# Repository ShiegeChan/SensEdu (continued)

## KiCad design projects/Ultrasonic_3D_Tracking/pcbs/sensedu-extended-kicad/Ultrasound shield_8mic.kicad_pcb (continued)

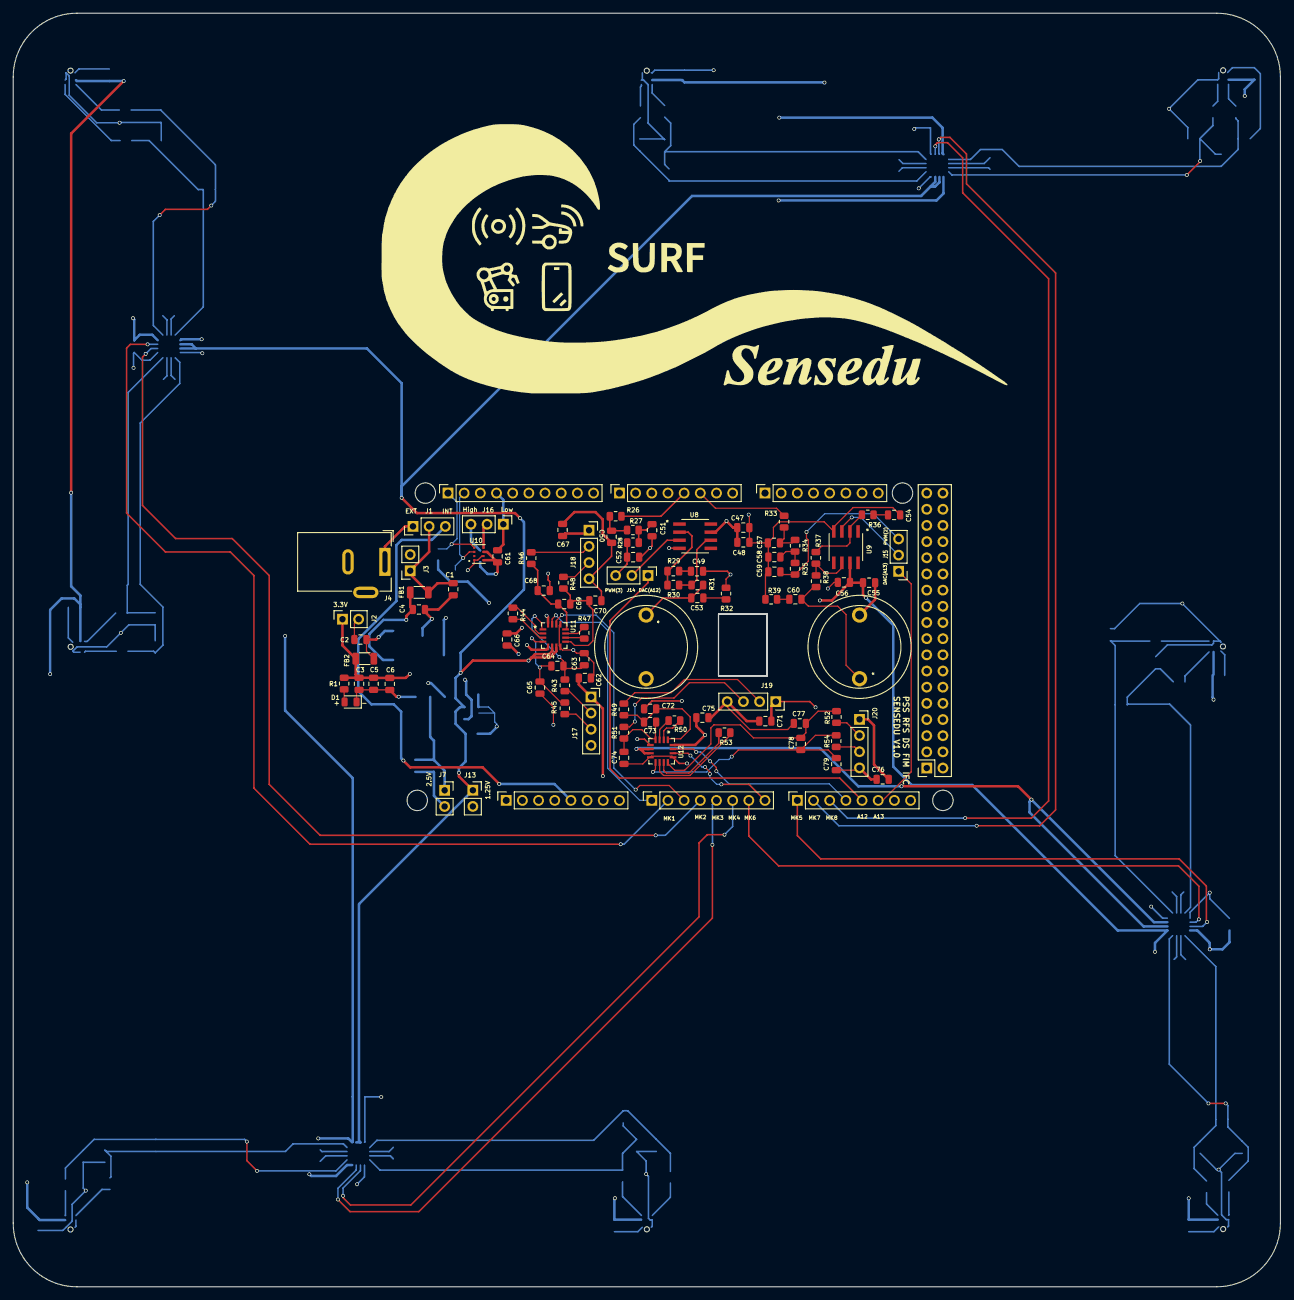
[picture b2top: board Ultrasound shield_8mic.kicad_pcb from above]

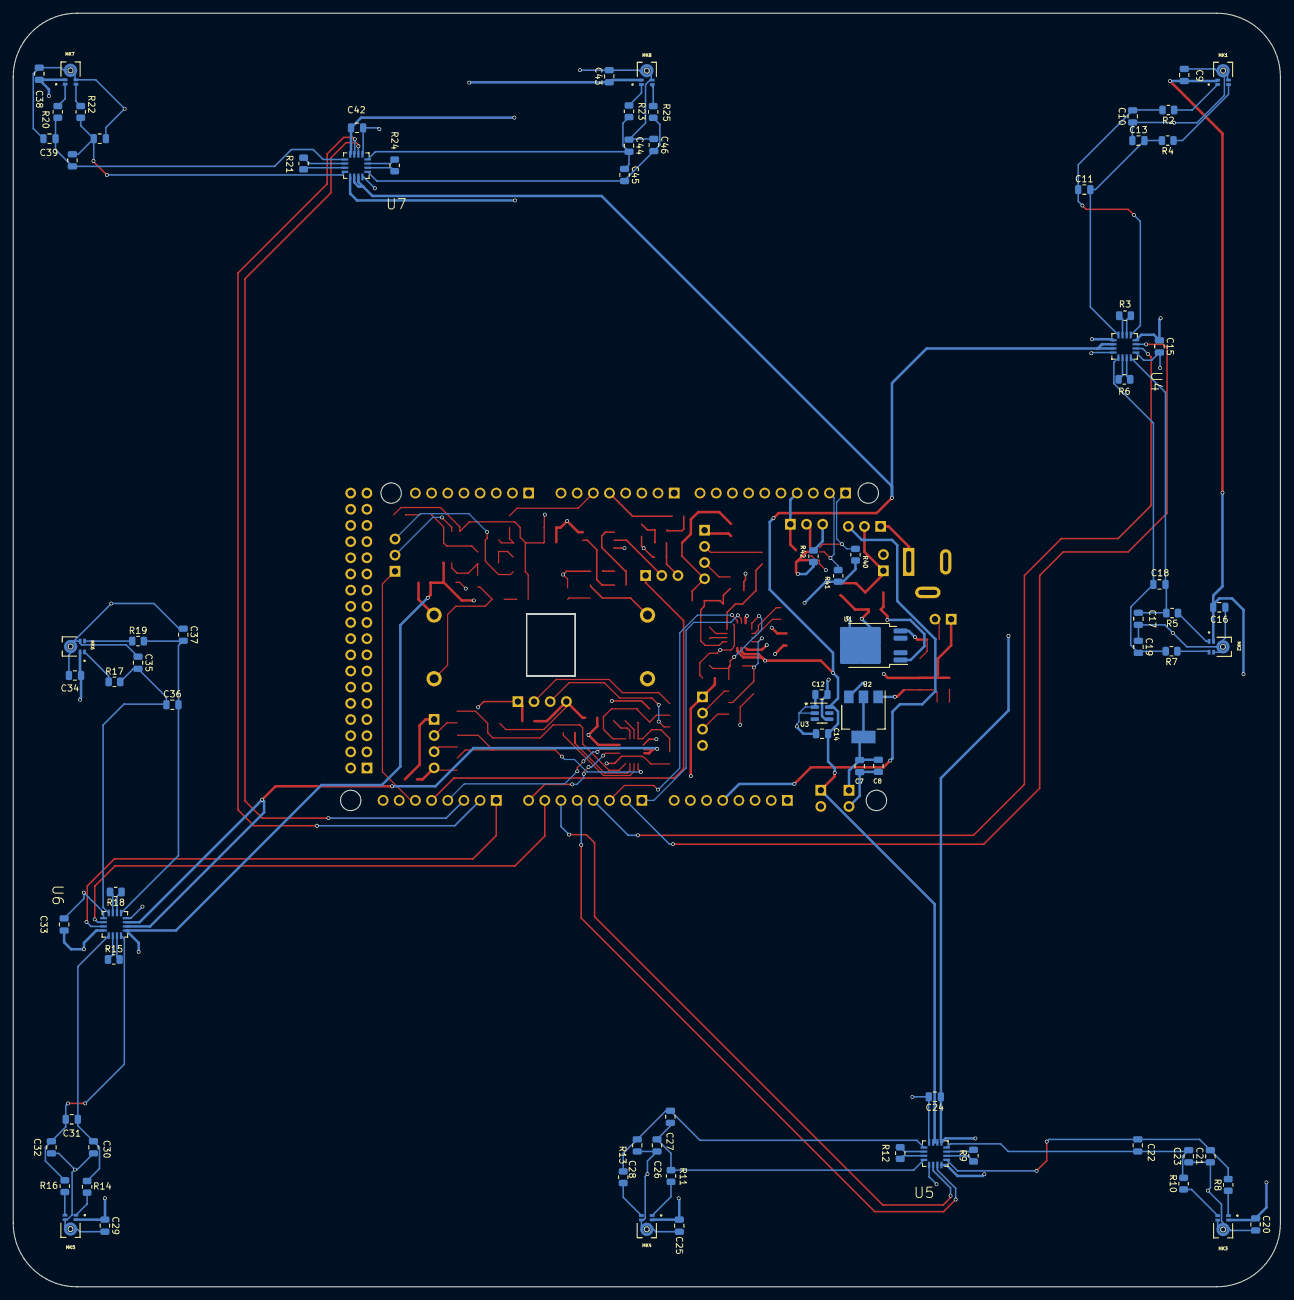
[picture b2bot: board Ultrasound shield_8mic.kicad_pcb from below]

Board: 4 copper layers, 199.0 x 200.0 mm, 182 parts (82 on the bottom side), 120 nets.

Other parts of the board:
MH1, MH2, MH5, MH6: MountingHole_3.2mm

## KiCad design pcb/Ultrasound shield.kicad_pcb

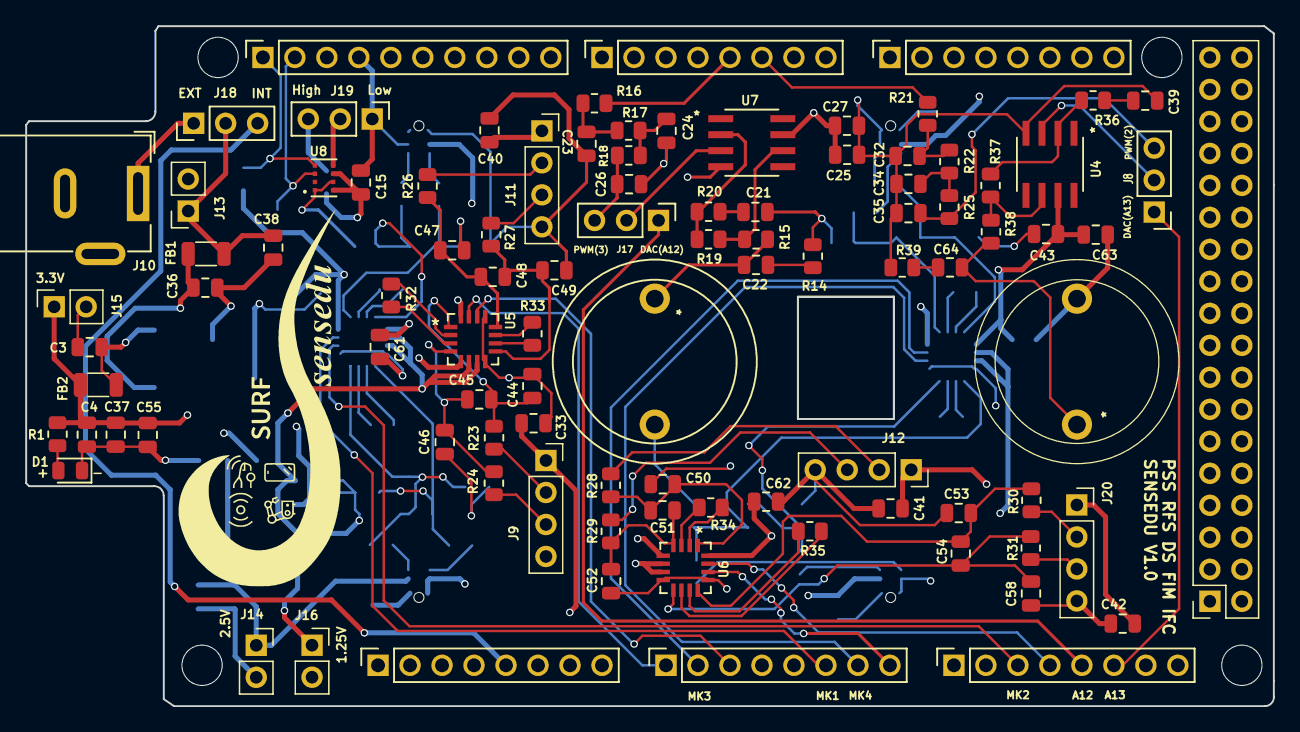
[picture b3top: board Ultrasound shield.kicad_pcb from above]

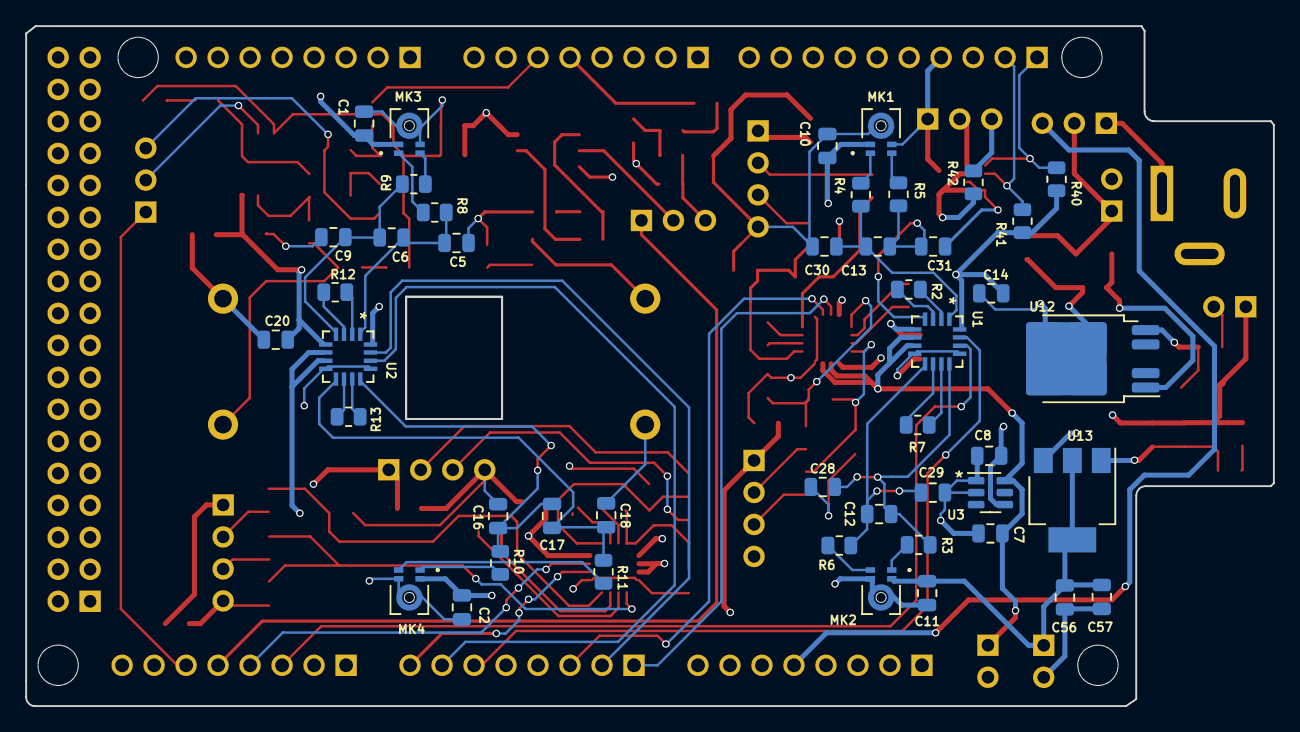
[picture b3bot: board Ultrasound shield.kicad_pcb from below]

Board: 4 copper layers, 99.1 x 54.0 mm, 146 parts (46 on the bottom side), 92 nets.

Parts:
C1, C2, C4, C8, C10, C11, C15, C21, C27, C33, C36, C39, C40, C41, C42, C55, C57, C63: 100n; C_0805_2012Metric
C3, C37, C38, C56: 10u; C_0805_2012Metric
C5, C9, C16, C18, C28, C29, C30, C31, C44, C46, C47, C49, C50, C52, C53, C58: 100p; C_0805_2012Metric
C6, C12, C13, C17, C45, C48, C51, C54: 470p; C_0805_2012Metric
C7, C14, C20, C25, C43, C61, C62: 1u; C_0805_2012Metric
C22, C64: DNI; C_0805_2012Metric
C23, C24, C26, C32, C34, C35: 1n; C_0805_2012Metric
D1: LED; LED_0805_2012Metric
FB1, FB2: FerriteBead; L_1206_3216Metric12
J1: Power; PinSocket_1x08_P2.54mm_Vertical
J2: PWM; PinSocket_1x10_P2.54mm_Vertical
J3, J5: Analog; PinSocket_1x08_P2.54mm_Vertical
J4: PWM; PinSocket_1x08_P2.54mm_Vertical
J6: Communication; PinSocket_1x08_P2.54mm_Vertical
J7: Digital; PinSocket_2x18_P2.54mm_Vertical
J8, J17, J18, J19: Conn_03x01; PinHeader_1x03_P2.54mm_Vertical
J9, J11, J12, J20: Conn_01x04_Pin; PinSocket_1x04_P2.54mm_Vertical
J10: Barrel_Jack_Switch; BarrelJack_Wuerth_6941xx301002
J13, J14, J15, J16: Conn_02x01; PinSocket_1x02_P2.54mm_Vertical
LS1, LS2: Speaker_Ultrasound; 328ST16M_Speaker
MH1, MH2, MH5, MH6: MountingHole_3.2mm
MK1, MK2, MK3, MK4: IM73A135V01XTSA1; MIC_IM73A135V01XTSA1
R1: 47; R_0805_2012Metric
R2, R7, R12, R13, R20, R32, R33, R34, R35, R36: 1k; R_0805_2012Metric
R3, R4, R5, R6, R8, R9, R10, R11, R23, R24, R26, R27, R28, R29, R30, R31: 3.9k; R_0805_2012Metric
R14, R39: DNI; R_0805_2012Metric
R15, R38: 0; R_0805_2012Metric
R16, R17, R18, R21, R22, R25: 4.7k; R_0805_2012Metric
R19, R37: 3k; R_0805_2012Metric
R40, R41, R42: 10k; R_0805_2012Metric
U1, U2, U5, U6: AD8426ACPZ-R7; QFN65P400X400X100-16N
U3: LT1790ACS6-1.25; TSOT-23-6
U4, U7: R_8_ADI; ADA4891-1ARZ
U8: DPS310XTSA1; XDCR_DPS310XTSA1
U12: TLS850C2TE_V33; TO-252-4
U13: NCP1117-2.5_SOT223; SOT-223-3_TabPin2

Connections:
+1.25V_REF: C7.2, J16.1, U1.6 (REF1), U1.7 (REF2), U2.6 (REF1), U2.7 (REF2), U3.6 (Vout), U5.6 (REF1), U5.7 (REF2), U6.6 (REF1), U6.7 (REF2)
+2.5V: C1.1, C2.1, C10.1, C11.1, C33.1, C40.1, C41.1, C42.1, C56.1, C57.1, J9.1, J11.1, J12.1, J14.1, J20.1, MK1.2 (VDD), MK2.2 (VDD), MK3.2 (VDD), MK4.2 (VDD), U13.2 (VO)
+3.3V: C4.1, C8.1, C14.1, C15.1, C20.1, C25.2, C27.2, C37.1, C43.2, C55.1, C61.1, C62.1, C63.2, FB2.2, J15.1, R1.1, R40.2, R41.1, R42.2, U1.5 (+VS), U1.16 (+VS), U2.5 (+VS), U2.16 (+VS), U3.4 (Vin), U4.7 (VS+), U5.5 (+VS), U5.16 (+VS), U6.5 (+VS), U6.16 (+VS), U7.7 (VS+), U8.6 (VDDIO), U8.8 (VDD), U13.3 (VI)
/*2: J4.6, R21.2
/*3: J4.5, R16.2
/A0: J3.1, U5.15 (OUT1)
/A1: J3.2, U2.15 (OUT1)
/A2: J3.3, U5.14 (OUT2)
/A5: J3.6, U1.15 (OUT1)
/A6: J3.7, U2.14 (OUT2)
/A7: J3.8, U6.14 (OUT2)
/A10: J5.3, U1.14 (OUT2)
/A11: J5.4, U6.15 (OUT1)
/SCL1: J2.1, R40.1, U8.4 (SCK)
/SDA1: J2.2, R41.2, U8.3 (SDI)
A12: J5.5, J17.1 (A)
A13: J5.6, J8.1 (A)
GND: C1.2, C2.2, C3.2, C4.2, C5.1, C7.1, C8.2, C9.1, C10.2, C11.2, C14.2, C15.2, C16.1, C18.1, C20.2, C21.2, C23.2, C24.2, C25.1, C26.2, C27.1, C28.1, C29.1, C30.1, C31.1, C32.2, C33.2, C34.2, C35.2, C36.2, C37.2, C38.2, C39.2, C40.2, C41.2, C42.2, C43.1, C44.1, C46.1, C47.1, C49.1, C50.1, C52.1, C53.1, C55.2, C56.2, C57.2, C58.1, C61.2, C62.2, C63.1, D1.1 (K), J1.6, J1.7, J2.4, J7.1, J7.2, J9.4, J10.2, J11.4, J12.4, J13.2, J14.2, J15.2, J16.2, J19.1 (A), J20.4, LS1.2, LS2.2, MK1.4 (GND), MK1.5_1 (GND), MK1.5_2 (GND), MK2.4 (GND), MK2.5_1 (GND), MK2.5_2 (GND), MK3.4 (GND), MK3.5_1 (GND), MK3.5_2 (GND), MK4.4 (GND), MK4.5_1 (GND), MK4.5_2 (GND), R14.1, R39.1, U1.8 (-VS), U1.13 (-VS), U2.8 (-VS), U2.13 (-VS), U3.1 (GND), U3.2 (GND), U4.4 (VS-), U5.8 (-VS), U5.13 (-VS), U6.8 (-VS), U6.13 (-VS), U7.4 (VS-), U8.1 (GND), U8.7 (GND), U12.3 (GND), U13.1 (GND)
unnamed: C21.1, R20.2
unnamed: C22.1, LS1.1, R15.2
unnamed: C22.2, R14.2
unnamed: C23.1, R16.1, R17.1
unnamed: C24.1, R17.2, R18.1
unnamed: C32.1, R21.1, R22.1
unnamed: C34.1, R22.2, R25.1
unnamed: C39.1, R36.2
unnamed: C64.1, LS2.1, R38.2
unnamed: C64.2, R39.2
unnamed: D1.2 (A), R1.2
unnamed: J1.5, J18.3 (B)
unnamed: C35.1, J8.3 (B), R25.2
unnamed: J8.2 (C), U4.3 (IN+)
unnamed: J9.2, R23.1
unnamed: J9.3, R24.1
unnamed: J11.2, R26.1
unnamed: J11.3, R27.1
unnamed: J12.2, R28.1
unnamed: J12.3, R29.1
unnamed: C38.1, FB1.1, J13.1, J18.2 (C)
unnamed: C26.1, J17.3 (B), R18.2
unnamed: J17.2 (C), U7.3 (IN+)
unnamed: J10.1, J18.1 (A)
unnamed: J19.3 (B), R42.1
unnamed: J19.2 (C), U8.5 (SDO)
unnamed: J20.2, R30.1
unnamed: J20.3, R31.1
unnamed: MK1.1 (OUTPUT+), R4.1
unnamed: MK1.3 (OUTPUT-), R5.1
unnamed: MK2.1 (OUTPUT+), R3.1
unnamed: MK2.3 (OUTPUT-), R6.1
unnamed: MK3.1 (OUTPUT+), R8.1
unnamed: MK3.3 (OUTPUT-), R9.1
unnamed: MK4.1 (OUTPUT+), R10.1
unnamed: MK4.3 (OUTPUT-), R11.1
unnamed: R2.1, U1.2 (RG1)
unnamed: R2.2, U1.3 (RG1)
unnamed: R7.1, U1.10 (RG2)
unnamed: R7.2, U1.11 (RG2)
unnamed: R12.1, U2.2 (RG1)
unnamed: R12.2, U2.3 (RG1)
unnamed: R13.1, U2.10 (RG2)
unnamed: R13.2, U2.11 (RG2)
unnamed: R32.1, U5.2 (RG1)
unnamed: R32.2, U5.3 (RG1)
unnamed: R33.1, U5.10 (RG2)
unnamed: R33.2, U5.11 (RG2)
unnamed: R34.1, U6.2 (RG1)
unnamed: R34.2, U6.3 (RG1)
unnamed: R35.1, U6.10 (RG2)
unnamed: R35.2, U6.11 (RG2)
unnamed: C13.2, C31.2, R5.2, U1.4 (+IN1)
unnamed: C12.2, C29.2, R6.2, U1.9 (+IN2)
unnamed: C13.1, C30.2, R4.2, U1.1 (-IN1)
unnamed: C12.1, C28.2, R3.2, U1.12 (-IN2)
unnamed: C6.2, C9.2, R9.2, U2.4 (+IN1)
unnamed: C17.2, C18.2, R11.2, U2.9 (+IN2)
unnamed: C5.2, C6.1, R8.2, U2.1 (-IN1)
unnamed: C16.2, C17.1, R10.2, U2.12 (-IN2)
unnamed: R36.1, R37.1, U4.2 (IN-)
unnamed: R37.2, R38.1, U4.6 (OUT)
unnamed: C45.2, C46.2, R24.2, U5.4 (+IN1)
unnamed: C48.2, C49.2, R27.2, U5.9 (+IN2)
unnamed: C44.2, C45.1, R23.2, U5.1 (-IN1)
unnamed: C47.2, C48.1, R26.2, U5.12 (-IN2)
unnamed: C51.2, C52.2, R29.2, U6.4 (+IN1)
unnamed: C54.2, C58.2, R31.2, U6.9 (+IN2)
unnamed: C50.2, C51.1, R28.2, U6.1 (-IN1)
unnamed: C53.2, C54.1, R30.2, U6.12 (-IN2)
unnamed: R19.1, R20.1, U7.2 (IN-)
unnamed: R15.1, R19.2, U7.6 (OUT)
unnamed: C36.1, FB1.2, U12.1 (I)
unnamed: C3.1, FB2.1, U12.5 (Q)

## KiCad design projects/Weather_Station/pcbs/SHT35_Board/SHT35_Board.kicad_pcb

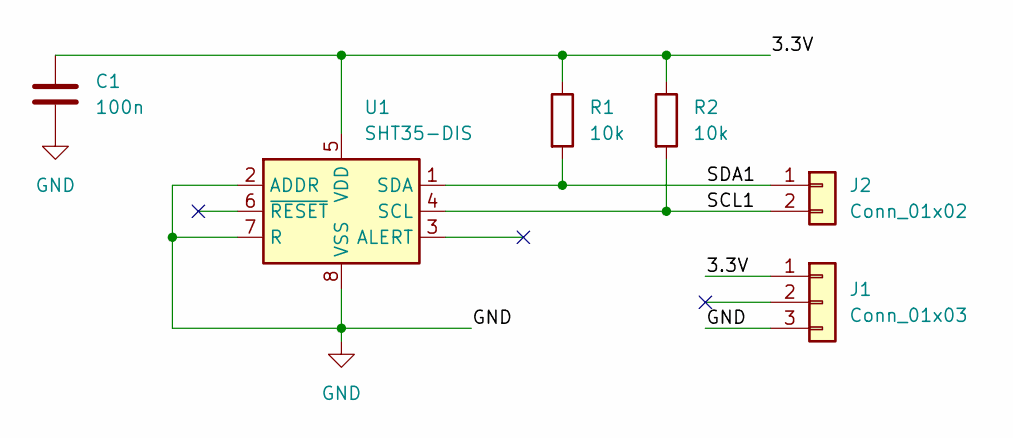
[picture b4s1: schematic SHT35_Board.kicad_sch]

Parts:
C1: 100n; C_0805_2012Metric_Pad1.18x1.45mm_HandSolder
J1: Conn_01x03; PinHeader_1x03_P2.54mm_Vertical
J2: Conn_01x02; PinHeader_1x02_P2.54mm_Vertical
R1, R2: 10k; R_0805_2012Metric_Pad1.20x1.40mm_HandSolder
U1: SHT35-DIS; Sensirion_DFN-8-1EP_2.5x2.5mm_P0.5mm_EP1.1x1.7mm

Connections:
/3.3V: C1.1, J1.1, R1.1, R2.1, U1.5 (VDD)
/SCL1: J2.2, R2.2, U1.4 (SCL)
/SDA1: J2.1, R1.2, U1.1 (SDA)
GND: C1.2, J1.3, U1.2 (ADDR), U1.7 (R), U1.8 (VSS), U1.9 (VSS)

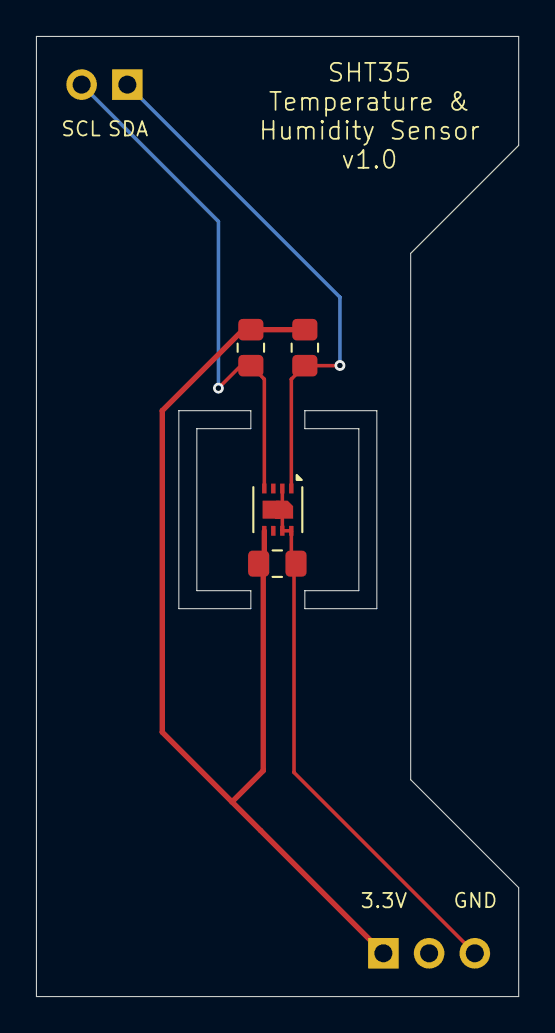
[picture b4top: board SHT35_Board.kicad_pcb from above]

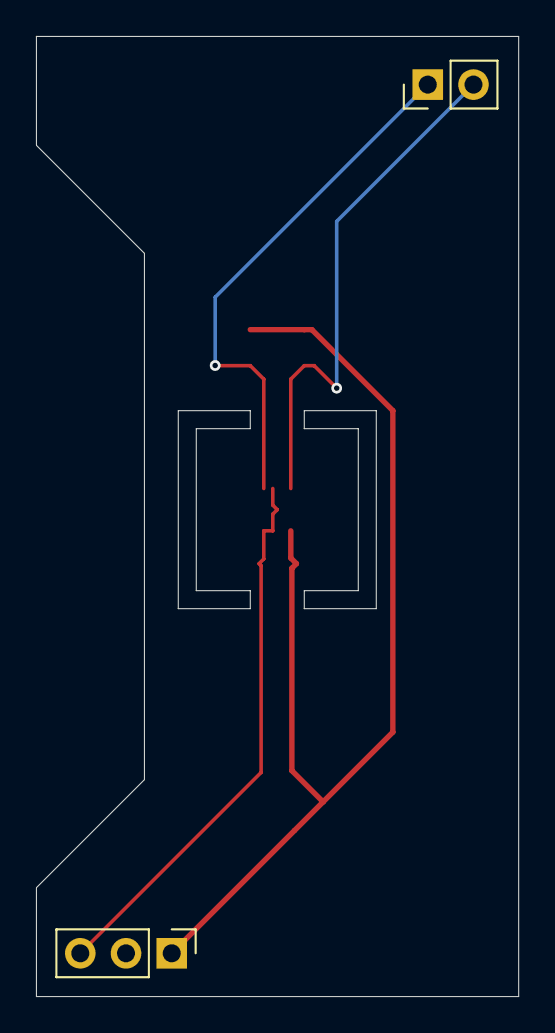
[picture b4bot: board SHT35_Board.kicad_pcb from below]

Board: 2 copper layers, 26.8 x 53.3 mm, 6 parts (2 on the bottom side), 4 nets.

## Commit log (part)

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2025-05-28 additional dataset
2025-05-29 cleaned up main script
2025-05-29 button press logic
2025-06-06 Fixed ADC conflict with FMCW radar
2025-06-13 first working measurement tracking
2025-06-13 Internal firmware error notification for MATLAB
2025-06-13 Basic weather status example using DPS310
2025-06-13 Added XENSIV pressure sensor github link to acknowledgments
2025-06-13 renaming driver to old version
2025-06-16 updates-tracking
2025-06-16 attempt into flexible threshold calculations
2025-06-18 clean unnecessary parts
2025-06-18 matlab scripts restructure
2025-06-18 keys pressing and square wave plotting
2025-06-18 timing calculation corrections for maximums
2025-06-20 split local functions onto separate files
2025-06-20 new recorded data test script
2025-06-25 MATLAB & Arduino scripts for single board FMCW radar distance measurement in progress
2025-07-21 FMCW distance measurement with single board update
2025-07-24 Added SHT35 Board PCB files and Weather_Station example updated
2025-07-28 todo projects updated
2025-07-28 EMG docs: introduction + biological bg draft
2025-08-01 EMG docs: electrode connectivity setup draft
2025-08-04 EMG docs: temporal cleanup for merge
2025-08-11 Added documentation for UltraSound Wifi example
2025-10-15 Feature: Support independent timers for ADCs with different sampling rates
2025-10-21 Rename the test for different sampling rates
2025-10-21 st test: styling corrections for consistency
2025-10-27 Removed renamed and deprecated files from feature branch
2025-10-27 ADC2 sample rate in matlab same as arduino sketch
2025-10-30 First working weather station using both sensors: humidity and pressure sensor
2025-11-07 Project documentation
2025-11-07 refactor: delete main repo deployment
2025-11-07 docs: update main sensedu description
2025-11-07 docs: update the project list
2025-11-10 docs: updated roadmap for contributing page
2025-11-12 docs: Add contributing style guidelines
2025-11-12 docs: Add generic pull request template
2025-11-12 refactor: Rewrite PR template for convenience
2025-11-13 refactor: Update lib styling page with new README
2025-11-14 intersteps
2025-11-14 refactor: Remove italics for public\private (#41)
2025-11-14 refactor: Add temporal -temp suffix to all docs
2025-11-14 fix: rename all the links across the docs
2025-11-26 feat: Add Record_Audio example
    Records audio and saves it in .wav file.
2025-11-27 feat: Weather station project update
    Adding a showcase in the documentation file.
2025-11-28 feat: Fix DRC errors and warnings
    Updated footprint links
    Updated schematic symbol for LT1790 to remove warnings
2025-11-28 refactor: Change the trigger for Record_Audio
    Change buffer size to the multiple of 32-bytes
    Move matlab trigger to request a certain amount of loops
    Reduce hearable audio "cuts"
2025-12-02 Fix: coding style (#56)
2025-12-02 feat: fix DRC and ERC errors and warnings
    first clean version
2025-12-03 feat: Implemented loop for bit modulation
2025-12-03 feat: Updated weather station documentation (PR comments resolved)
2025-12-03 fix: broken link in pr template
2025-12-04 feat: TX with two DAC
2025-12-04 fix: Remove self-host tests
2025-12-05 feat: Checked and polished MATLAB script
    Added audio recording visualization
    Added new recorded audio example
    Added example documentation
2025-12-05 Polishin pt1
2025-12-10 New PDF on the docu page
2025-12-11 feat: Receiving arbitrary data length in matlab scripts
2025-12-12 code optimization
2025-12-12 refactor: Edit speaker/mic symbols and polish
2025-12-15 refactor: Update pcb docs page with new schematic and rendered images
2025-12-15 Basic_Ultrasound.py and Basic_UltraSound_4CH.py review and polish
2025-12-16 Minor corrections to documentation and matlab file of Basic UltraSound example in Python
2025-12-18 Refactor: Main Projects page on SensEdu website
2025-12-18 feat: Reimplement adc modes and SR architecture
    Implement proper single channel software polling for new adc driver
    Refactor all ADC names to a new code naming style
    Rework adc examples structure
    Add optional overrun interrupts
2025-12-18 chore: Add comments for public API
    Rearrange adc errors
2025-12-18 refactor: Add new get_adc_channel w/o huge switch
2025-12-18 refactor: Better overwrite & working 3ch dma norm
2025-12-18 feat: Finish cont multi-ch polling with warning
    Add proper interrupts for OVR flags
2025-12-18 feat: multi-channel one-shot soft polling
2025-12-18 refactor: Redo sample time config w/o huge switch
2025-12-18 chore: Remove redundant examples and rename others
2025-12-18 feat: Color the syntax for new lib functions
    Refactor ADCx3 and Blink examples
2025-12-18 feat: Add new DMA example with HT flag
    Rename DAC examples
2025-12-18 refactor: Update ultrasonic examples with new adc
2025-12-18 fix: text nitpick (#72)
2026-01-02 refactor: Record_Audio example
    New transmission scripts for handling partial chunks
    Code Comment formating
2026-01-05 refactor: Ultrasound distance acquisition example
    Remove the files for 8 microphone board
2026-01-13 feat: Rework DMA driver & implement ADC MPU config
    Disable cache with proper MPU config
    Refactor copy-paste logic into indexable maps
    Generalize some DMA functionality for ADC and DAC
    Remove every cache invalidation
    Rewrite DMA errors
    Refactor all function and var names
2026-01-14 feat: FSK demodulation working
2026-01-16 feat: Dynamic LUT implemented
2026-01-19 feat: Code polished
2026-01-21 feat: Change waves to 32kHz and 34kHz
    LUTs have now different sizes
2026-01-23 refactor: Fix styling
2026-01-23 fix: Correct MPU calculation & ADC triggering
    Fixed unassigned triggers for ADC2 & ADC3
    Updated stable MPU calculations
2026-02-04 Progress in pcb routing
2026-02-04 pcb routing finished
    very messy
2026-02-09 refactor: Code styling fixed
2026-02-13 feat: Implement audio recording
    - Add recording duration in seconds which is transmitted to the firmware
2026-02-14 in works
2026-02-18 docs: Starting the introduction of FSK
2026-02-19 refactor: Update ultrasonic comments
2026-02-19 feat: Implement FSK TX with const samples per char
    - Independent of requested frequency
2026-02-20 refactor: fmcw .ino script variable name changes
    fmcw new communication function
2026-02-20 refactor: Print error code in DAC examples
2026-02-20 fix: Typo for pi
2026-02-24 feat: Add wires FSK with MATLAB
2026-02-25 refactor: Clean up the decision block
2026-02-26 feat: Redraw PCB layout
    - Change supply polarity and pin numbers of ADA4511
    - Change cap of switches to 100n to reduce bom
    - Change supply of sensors to unison 3.3V
    - Rearrange mic and amps pins
    - Add mountains
    - Add Infineon logo
2026-02-27 feat: Implement real time wireless FSK
2026-02-27 refactor: Rearrange folder structure
2026-03-05 chore: Fix styling
2026-03-06 chore: Remove old schematics
2026-03-06 chore: Update schematics
2026-03-10 Fix: FMCW Matlab script doesn't boot on the first run
    Serial communication problem resolved
2026-03-10 docs: Add info about new IC & rearrangement of PCB
    - New humidity sensor
    - Rearrangement of components to facilitate easier reading
    - Increase of picture quality and quantity
    - Provided new tables for updated connections
2026-03-11 PR suggestions resolved
2026-03-11 fix: Add proper sizes and pins for ranging
2026-03-13 Added New Example
2026-03-16 docs: Updated Transmitter docs
2026-03-18 docs: FSK docs finished
    I think I have shown a lot of code, but tell me what do you think
2026-03-23 fix: more efficient computation for envelope and peak search
2026-03-24 feat: Upgrade speaker simulation to realistic one
2026-03-25 feat: Improve PCB design after tests of rev 0.8
    - Added new generation of humidity sensor
    - New silkscreen information for different components
    - Added additional testpoints
    - Removed PWM path for ultrasound transmitter
2026-03-26 docs: fix of req. changes and info on new sensor
    - half spacing between every value and its unit symbol
    - correction of numerous formatting errors
    - specified information about use of pressure and humidity sensor
    - removed info about digital switches
    - replacement of SHT35-DIS with SHT40-AD1F/P
2026-03-26 docs: update of PCB pictures
    - new pictures of 0.9 version PCB
    - clarified correct I2C bus
2026-03-26 feat: Enable DAC buffer in SensEdu Library
    - Add a documentation note on reasons for the dac buffer
2026-03-26 refactor: Remove unnecessary comments
    - Regenerate schematics
2026-03-26 feat: Reword FSK introduction a bit
    - Change navigation page order for FSK to appear higher
2026-03-27 fix: Add integer check for Goertzel coeff
2026-03-27 temp
2026-03-27 refactor: Move FMCW sims in a separate folder
2026-03-27 docs: Update timer errors and add notes for delays
2026-03-30 feat: Revamp DAC driver
    - Add timeout for blocking waits
    - Ensure valid single wave mode
    - Add protective null checks everywhere
    - Ensure sampling rate is the same in both channels
    - Explicitly check the channel validity everywhere
    - Replace singular definitions with arrays
2026-03-30 refactor: Replace int with bool for a burst flag
2026-03-30 fix: Rename broken case sensitive images
2026-04-01 refactor: ultrasonic projects
2026-04-01 docs: Add doxygen header for DMA files
2026-04-01 refactor: Add ADC timeouts and general comments
2026-04-03 feat: Add ADC circular examples for 1CH and 3CH
2026-04-15 fix: Outdated cache coherence example in docs
2026-04-20 added a figure for ultrasonic tracking paper
2026-04-28 fix: order of mics and other minors
2026-04-28 fix: Revert added measurements
2026-04-28 refactor: Add Sensirion SHT4X lib as a module
2026-04-28 refactor: Better styling for i2c scanner
2026-04-28 feat: Add refactored SHT4x example
    - Original one does not compile on Mbed core due to redeclaration
2026-04-28 refactor: Remove DSP368 lib & replace with module
2026-04-30 feat: Add dew point spread measurements
    - Add each metric classification
2026-05-05 feat: Add dew point classification
2026-05-08 feat: Improve pressure conversion formula
2026-05-15 docs: Write the weather station documentation
2026-05-15 feat: Add examples for temp/RH/pressure readings
2026-05-15 fix: DPS naming conflict
2026-05-18 refactor: Tighten Record_Audio cmd_start ordering
    - cmd_start emits the ACK before SensEdu_ADC_Start
    - process_usb_transfer picks the ready slot with the lowest sequence_id
    - MATLAB seg_is_valid now takes expected_session_id and the actual
    SEGMENT_SAMPLES
2026-05-18 refactor: Use bytes instead of samples in MATLAB
2026-05-19 refactor: Move audio to projects
2026-05-19 docs: Add initial draft for audio recording
2026-05-19 docs: Add section on the reasons for workaround
2026-05-22 feat: Improve stability with proper trim on fail
2026-05-22 docs: Firmware implementation sections
2026-06-01 Cleanup after paper
2026-06-03 docs: Polish MATLAB section & notes
2026-06-03 feat: Add showcase audio
2026-06-05 feat: Convert wav to opus & specify encoding
2026-06-05 docs: Add specific humidity section
2026-06-08 feat: Add `_C` pin shorts for ADC flexibility
    - Update setup pictures to SensEdu 0.8 PCB
2026-06-08 refactor: Cleanup arduino sketch
2026-06-11 feat: Add raw recorder + processor
2026-06-11 refactor: Cleanup EMG matlab folder
2026-06-11 refactor: Split main .m into more functions
2026-06-12 refactor: Improve comments for EMG functions in MATLAB
2026-06-15 refactor: Cleanup EMG functions comments
2026-06-16 refactor: Better EMG Init order
2026-06-16 feat: Add virtual Xbox pad for unsupported games
2026-06-17 fix: Change header pin layout for SensEdu 0.8+
2026-06-29 refactor: Improve USB noise picture
2026-06-29 refactor: Add warning on wrong USB chunk size
2026-06-29 feat: Add extended SensEdu PCB files
